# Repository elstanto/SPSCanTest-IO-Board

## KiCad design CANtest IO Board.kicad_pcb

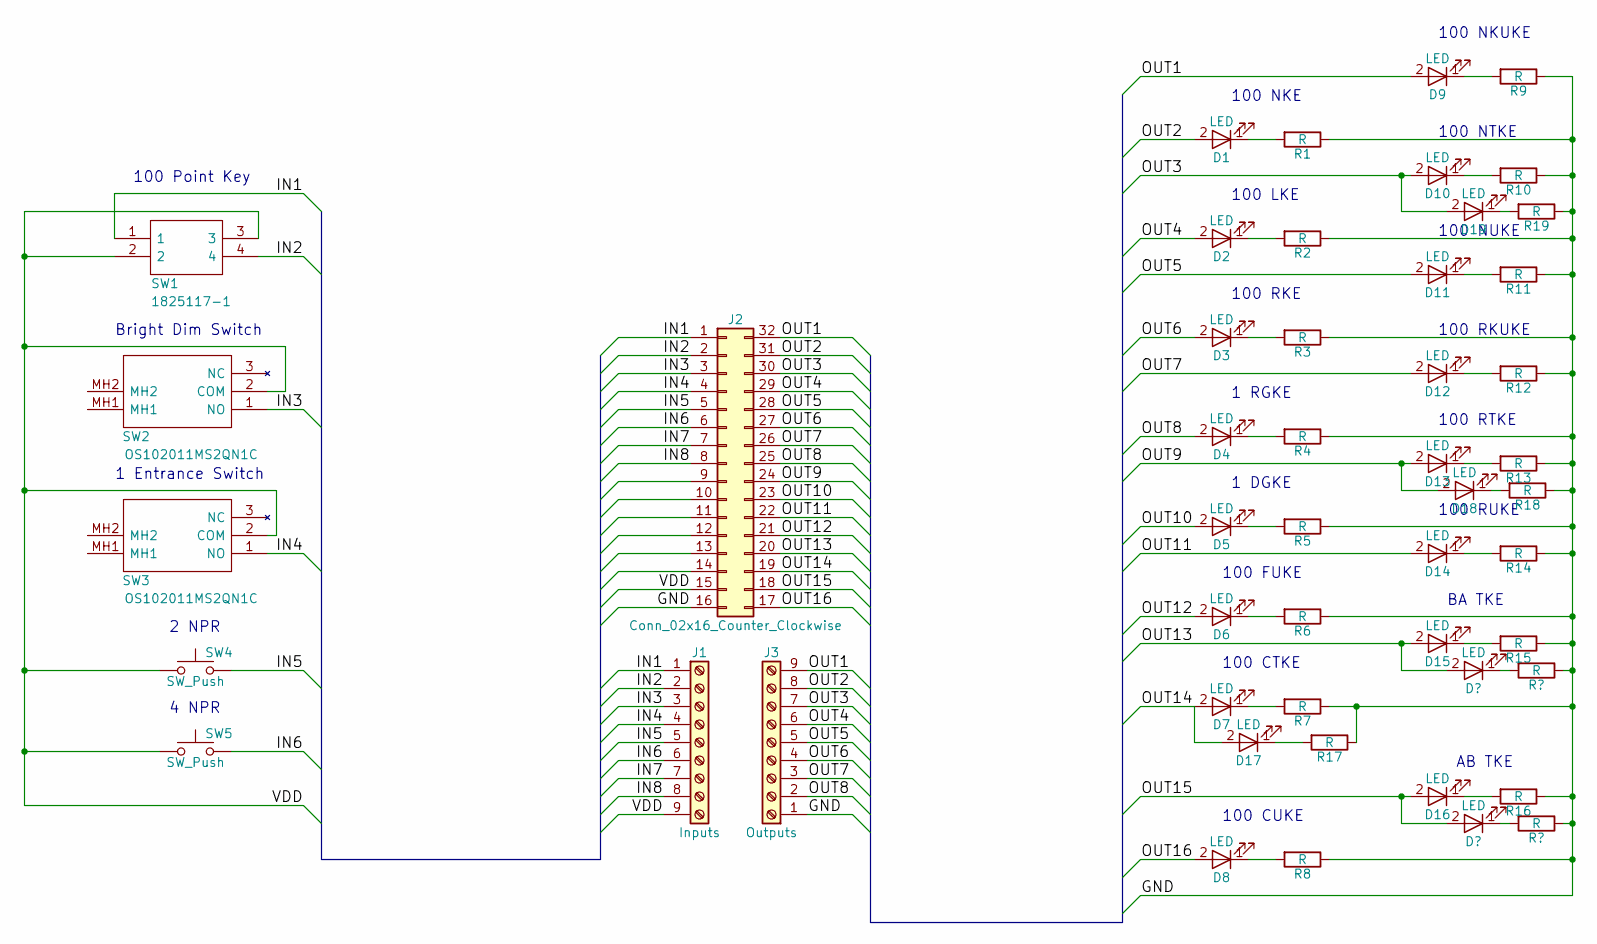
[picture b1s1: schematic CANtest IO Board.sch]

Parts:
D1, D2, D3, D4, D5: LED; LED_D3.0mm
D6, D7, D8, D9, D10, D11, D12, D13, D14, D15, D16, D17, D18, D19: LED; LED_Rectangular_W5.0mm_H2.0mm
J1: Inputs; TerminalBlock_Phoenix_MPT-2.54mm_9pol
J2: Conn_02x16_Counter_Clockwise; Pin_Header_Angled_2x16_Pitch2.54mm
J3: Outputs; TerminalBlock_Phoenix_MPT-2.54mm_9pol
R1, R2, R3, R4, R5, R6, R7, R8, R9, R10, R11, R12, R13, R14, R15, R16, R17, R18, R19: R; R_0805_HandSoldering
SW1: 1825117-1; SHDR4W87P0X320_1X4_1511X584X1100P; Manufacturer_Part_Number 1825117-1
SW2, SW3: OS102011MS2QN1C; Manufacturer_Part_Number OS102011MS2QN1C; Mouser Part Number 611-OS102011MS2QN1C
SW4, SW5: SW_Push; SW_SPST_KMR2

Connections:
/GND: J2.16, J3.1, R1.1, R2.1, R3.1, R4.1, R5.1, R6.1, R7.1, R8.1, R9.1, R10.1, R11.1, R12.1, R13.1, R14.1, R15.1, R16.1, R17.1, R18.1, R19.1; also elsewhere on the board
/IN1: J1.1, J2.1, SW1.1
/IN2: J1.2, J2.2, SW1.4
/IN3: J1.3, J2.3, SW2.1 (NO)
/IN4: J1.4, J2.4, SW3.1 (NO)
/IN5: J1.5, J2.5, SW4.2
/IN6: J1.6, J2.6, SW5.2
/IN7: J1.7, J2.7
/IN8: J1.8, J2.8
/OUT1: D9.2 (A), J2.32, J3.9
/OUT2: D1.2 (A), J2.31, J3.8
/OUT3: D10.2 (A), D19.2 (A), J2.30, J3.7
/OUT4: D2.2 (A), J2.29, J3.6
/OUT5: D11.2 (A), J2.28, J3.5
/OUT6: D3.2 (A), J2.27, J3.4
/OUT7: D12.2 (A), J2.26, J3.3
/OUT8: D4.2 (A), J2.25, J3.2
/OUT9: D13.2 (A), D18.2 (A), J2.24
/OUT10: D5.2 (A), J2.23
/OUT11: D14.2 (A), J2.22
/OUT12: D6.2 (A), J2.21
/OUT13: D15.2 (A), J2.20; also elsewhere on the board
/OUT14: D7.2 (A), D17.2 (A), J2.19
/OUT15: D16.2 (A), J2.18; also elsewhere on the board
/OUT16: D8.2 (A), J2.17
/VDD: J1.9, J2.15, SW1.2, SW1.3, SW2.2 (COM), SW3.2 (COM), SW4.1, SW5.1
unnamed: D1.1 (K), R1.2
unnamed: D2.1 (K), R2.2
unnamed: D3.1 (K), R3.2
unnamed: D4.1 (K), R4.2
unnamed: D5.1 (K), R5.2
unnamed: D6.1 (K), R6.2
unnamed: D7.1 (K), R7.2
unnamed: D8.1 (K), R8.2
unnamed: D9.1 (K), R9.2
unnamed: D10.1 (K), R10.2
unnamed: D11.1 (K), R11.2
unnamed: D12.1 (K), R12.2
unnamed: D13.1 (K), R13.2
unnamed: D14.1 (K), R14.2
unnamed: D15.1 (K), R15.2
unnamed: D16.1 (K), R16.2
unnamed: D17.1 (K), R17.2
unnamed: D18.1 (K), R18.2
unnamed: D19.1 (K), R19.2

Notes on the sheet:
100 Point Key
2 NPR
1 Entrance Switch
100 NKE
Bright Dim Switch
4 NPR
100 LKE
100 RKE
1 RGKE
1 DGKE
100 FUKE
100 CTKE
100 CUKE
100 NKUKE
100 NTKE
100 NUKE
100 RKUKE
100 RTKE
100 RUKE
BA TKE
AB TKE

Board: 2 copper layers, 50 parts (0 on the bottom side), 47 nets, no tracks yet.

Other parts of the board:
D20, D21: LED; LED_Rectangular_W5.0mm_H2.0mm
R20, R21: R; R_0805_HandSoldering

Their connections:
/GND: R20.1, R21.1; also elsewhere on the board
/OUT13: D20.2; also elsewhere on the board
/OUT15: D21.2; also elsewhere on the board
unnamed: D20.1, R20.2
unnamed: D21.1, R21.2

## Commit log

2019-11-28 Progress
2019-11-28 Progress2
